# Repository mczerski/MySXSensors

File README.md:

View this project on [CADLAB.io](https://cadlab.io/project/1672). 

# MySXSensors

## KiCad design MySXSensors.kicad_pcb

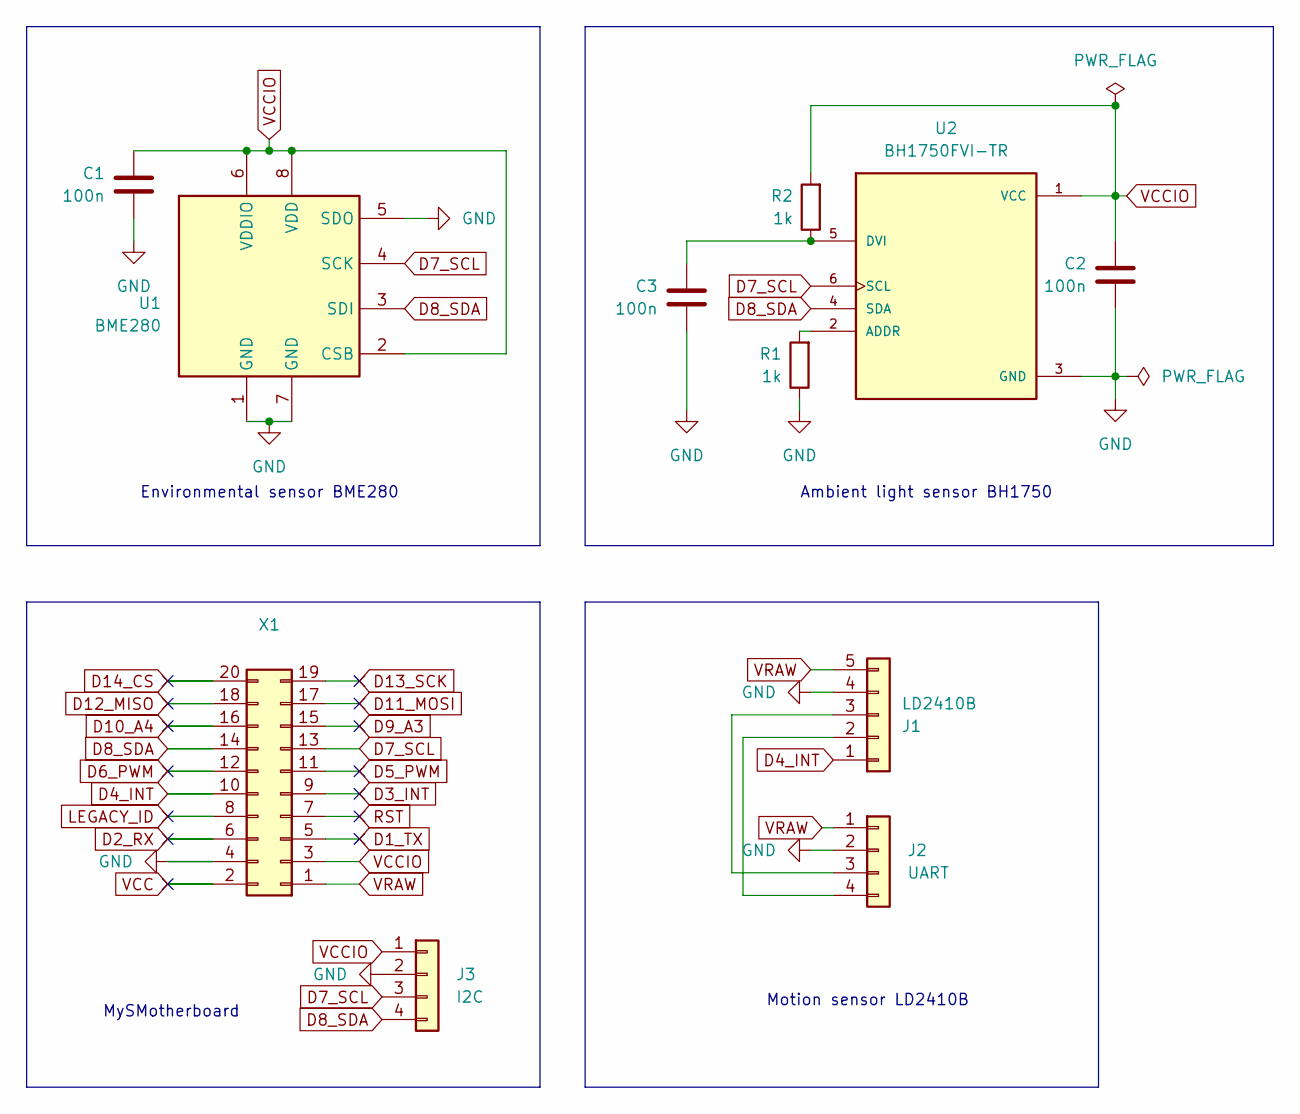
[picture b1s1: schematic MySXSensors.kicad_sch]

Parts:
C1, C2, C3: 100n; C_0402_1005Metric_Pad0.74x0.62mm_HandSolder
J1: LD2410B; PinHeader_1x05_P1.27mm_Vertical
J2: UART; JST-XH_S_4P-2.54MM-PIN1-RIGHT
J3: I2C; JST-XH_S_4P-2.54MM-PIN1-RIGHT
R1, R2: 1k; R_0603_1608Metric
U1: BME280; Bosch_LGA-8_2.5x2.5mm_P0.65mm_ClockwisePinNumbering
U2: BH1750FVI-TR; XDCR_BH1750FVI-TR
X1: FE10-2

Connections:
D1_TX: X1.5
D2_RX: X1.6
D3_INT: X1.9
D4_INT: J1.1, X1.10
D5_PWM: X1.11
D6_PWM: X1.12
D7_SCL: J3.3, U1.4 (SCK), U2.6 (SCL), X1.13
D8_SDA: J3.4, U1.3 (SDI), U2.4 (SDA), X1.14
D9_A3: X1.15
D10_A4: X1.16
D11_MOSI: X1.17
D12_MISO: X1.18
D13_SCK: X1.19
D14_CS: X1.20
GND: C1.2, C2.2, C3.2, J1.4, J2.2, J3.2, R1.1, U1.1 (GND), U1.5 (SDO), U1.7 (GND), U2.3 (GND), X1.4
LEGACY_ID: X1.8
unnamed: J1.2, J2.4
unnamed: J1.3, J2.3
unnamed: R1.2, U2.2 (ADDR)
unnamed: C3.1, R2.1, U2.5 (DVI)
RST: X1.7
VCC: X1.2
VCCIO: C1.1, C2.1, J3.1, R2.2, U1.2 (CSB), U1.6 (VDDIO), U1.8 (VDD), U2.1 (VCC), X1.3
VRAW: J1.5, J2.1, X1.1

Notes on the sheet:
Environmental sensor BME280
Motion sensor LD2410B
MySMotherboard
Ambient light sensor BH1750

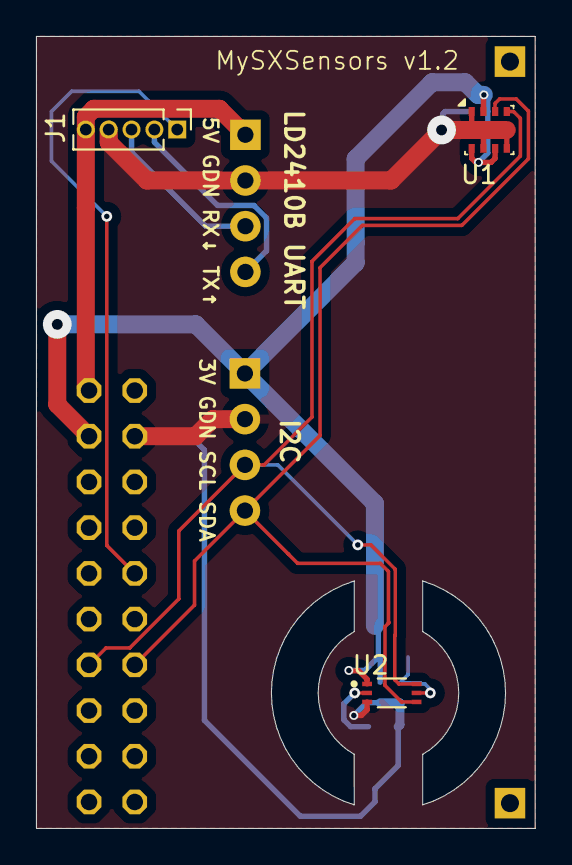
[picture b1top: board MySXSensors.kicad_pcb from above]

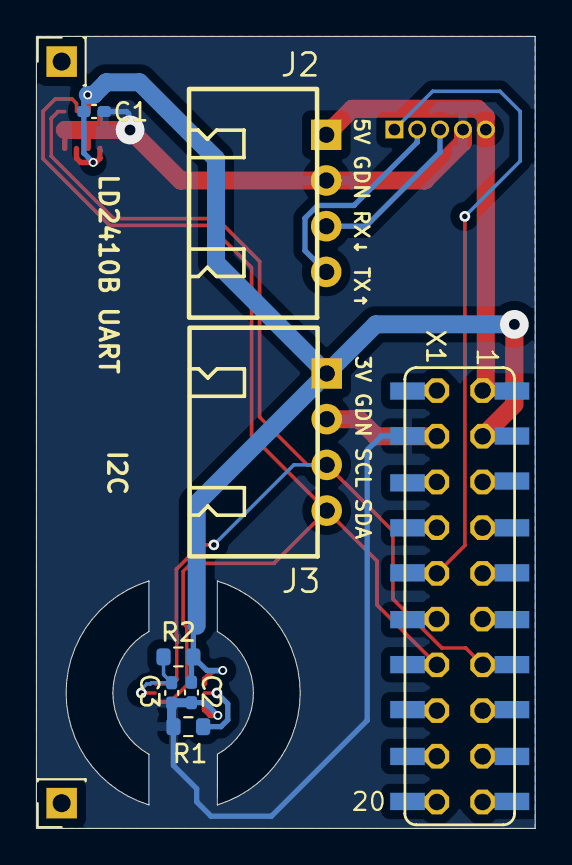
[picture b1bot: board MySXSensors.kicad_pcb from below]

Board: 2 copper layers, 27.7 x 44.0 mm, 12 parts (8 on the bottom side), 10 nets.

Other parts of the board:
L1: Lens

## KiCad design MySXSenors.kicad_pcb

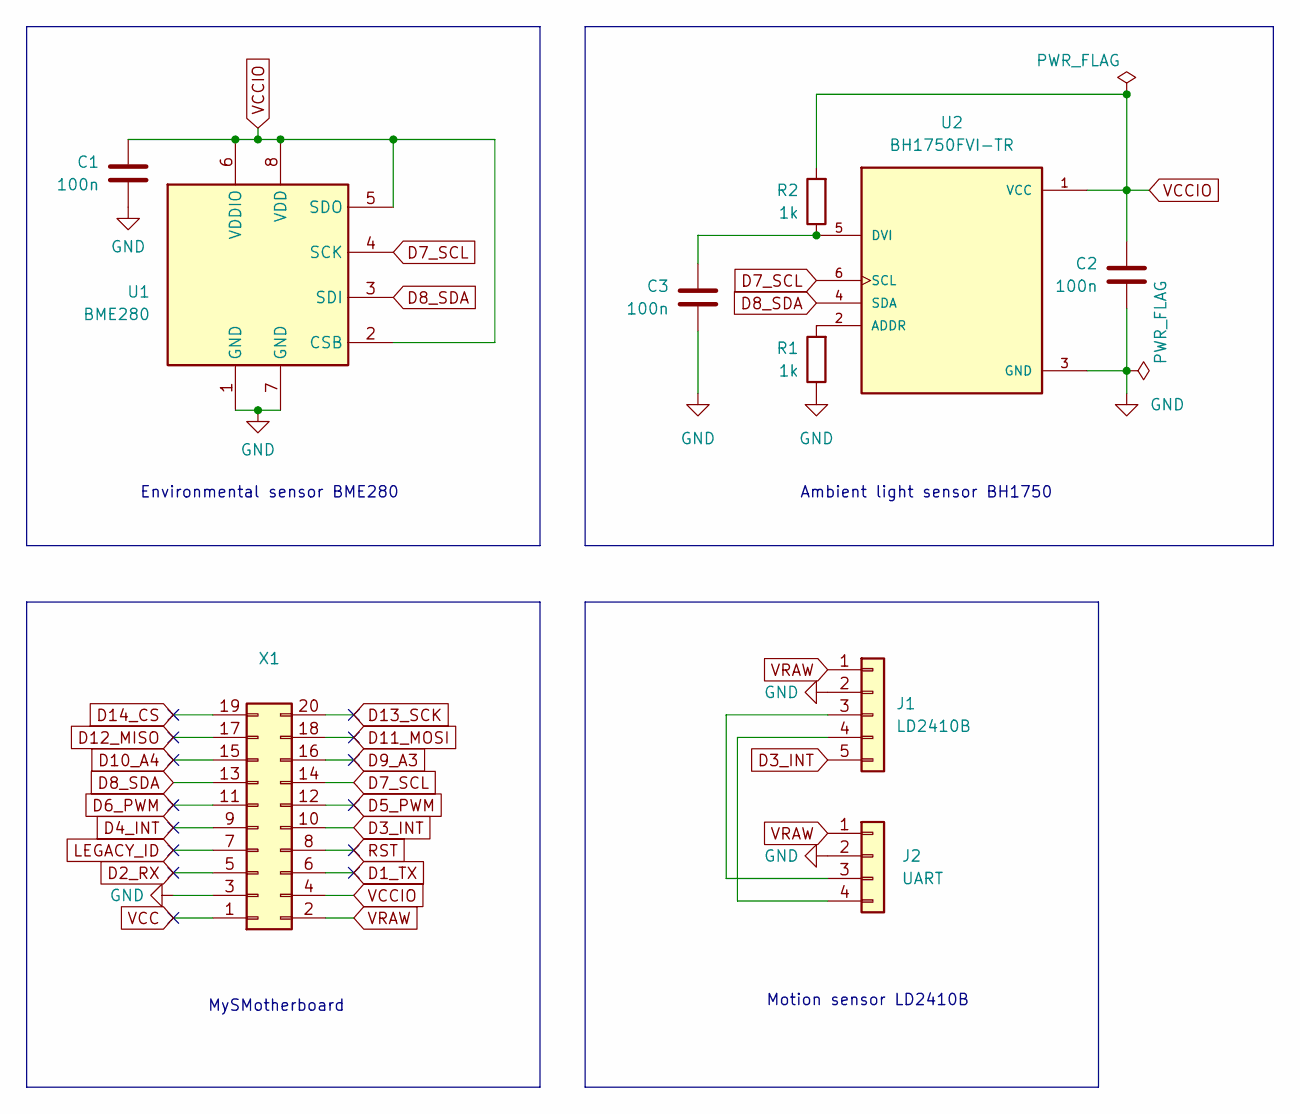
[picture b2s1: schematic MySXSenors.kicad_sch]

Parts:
C1, C2, C3: 100n; C_0402_1005Metric_Pad0.74x0.62mm_HandSolder
J1: LD2410B; PinHeader_1x05_P1.27mm_Vertical
J2: UART; PinHeader_1x04_P2.54mm_Horizontal
R1, R2: 1k; R_0603_1608Metric
U1: BME280; Bosch_LGA-8_2.5x2.5mm_P0.65mm_ClockwisePinNumbering
U2: BH1750FVI-TR; XDCR_BH1750FVI-TR
X1: FE10-2

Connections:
D1_TX: X1.6
D2_RX: X1.5
D3_INT: J1.5, X1.10
D4_INT: X1.9
D5_PWM: X1.12
D6_PWM: X1.11
D7_SCL: U1.4 (SCK), U2.6 (SCL), X1.14
D8_SDA: U1.3 (SDI), U2.4 (SDA), X1.13
D9_A3: X1.16
D10_A4: X1.15
D11_MOSI: X1.18
D12_MISO: X1.17
D13_SCK: X1.20
D14_CS: X1.19
GND: C1.2, C2.2, C3.2, J1.2, J2.2, R1.1, U1.1 (GND), U1.7 (GND), U2.3 (GND), X1.3
LEGACY_ID: X1.7
unnamed: J1.3, J2.3
unnamed: J1.4, J2.4
unnamed: R1.2, U2.2 (ADDR)
unnamed: C3.1, R2.1, U2.5 (DVI)
RST: X1.8
VCC: X1.1
VCCIO: C1.1, C2.1, R2.2, U1.2 (CSB), U1.5 (SDO), U1.6 (VDDIO), U1.8 (VDD), U2.1 (VCC), X1.4
VRAW: J1.1, J2.1, X1.2

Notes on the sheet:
Environmental sensor BME280
Motion sensor LD2410B
MySMotherboard
Ambient light sensor BH1750

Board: 2 copper layers, 10 parts (0 on the bottom side), 10 nets, no tracks yet.

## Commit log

2018-02-01 add uart
2018-06-10 make MysX connector smd mounted
2019-04-03 Backlink to CADLAB.io has been added.
2019-04-03 rename DTM and DTF signals
2024-09-28 fix project name
2024-09-28 version 1.0
2025-01-03 move 2x10 pin socket to bottom side (and other components) + change positions of sensors
2025-01-14 change BME280 addr pin to gnd + move vias outside of pads
2025-04-27 add gas sensor
2025-04-27 add external connector for I2C
2025-05-18 add JST connector + pin headers for stability
2025-07-05 change motion signal assignment to D4_INT
2025-07-05 add lens footprint
